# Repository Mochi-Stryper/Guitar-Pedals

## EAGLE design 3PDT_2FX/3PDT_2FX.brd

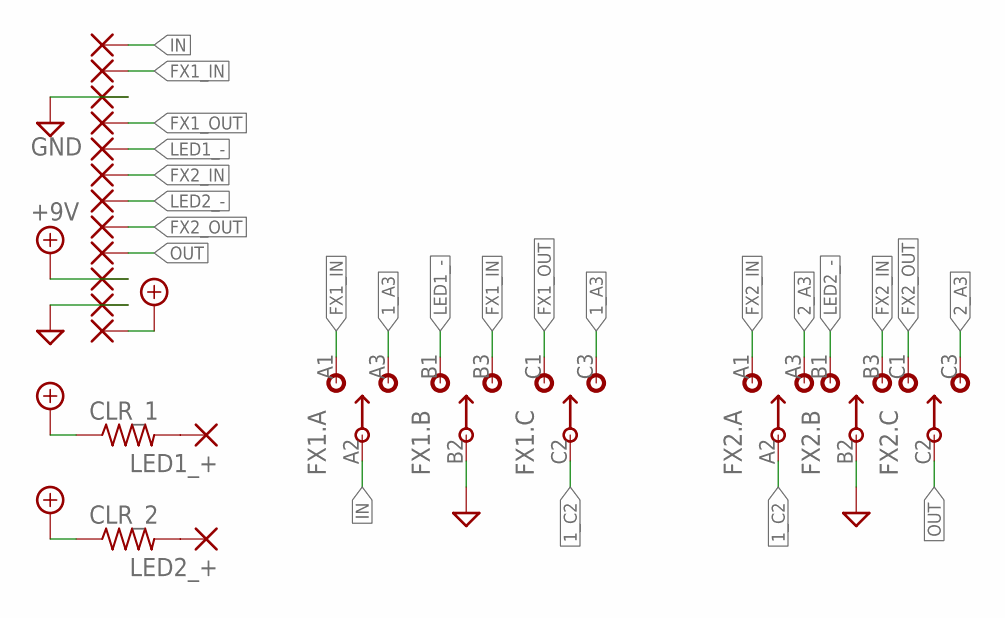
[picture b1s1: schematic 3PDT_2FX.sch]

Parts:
+9V, +9V1: 1,6/0,8
CLR_1, CLR_2: R-US_R0603; R0603
FX1, FX2: 3PDT.LUGS
FX1_IN, FX1_OUT, FX2_IN, FX2_OUT: 1,6/0,8
GND: 1,6/0,8
IN: 1,6/0,8
LED1_+, LED1_-, LED2_+, LED2_-: 1,6/0,8
OUT: 1,6/0,8
PAD3: 1,6/0,8

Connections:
1_A3: FX1.A3 (3), FX1.C3 (3)
1_C2: FX1.C2 (2), FX2.A2 (2)
2_A3: FX2.A3 (3), FX2.C3 (3)
+9V: +9V.1, +9V1.1, CLR_1.1, CLR_2.1
FX1_IN: FX1.A1 (1), FX1.B3 (3), FX1_IN.1
FX1_OUT: FX1.C1 (1), FX1_OUT.1
FX2_IN: FX2.A1 (1), FX2.B3 (3), FX2_IN.1
FX2_OUT: FX2.C1 (1), FX2_OUT.1
GND: FX1.B2 (2), FX2.B2 (2), GND.1, PAD3.1
IN: FX1.A2 (2), IN.1
LED1_-: FX1.B1 (1), LED1_-.1
LED2_-: FX2.B1 (1), LED2_-.1
unnamed: CLR_1.2, LED1_+.1
unnamed: CLR_2.2, LED2_+.1
OUT: FX2.C2 (2), OUT.1

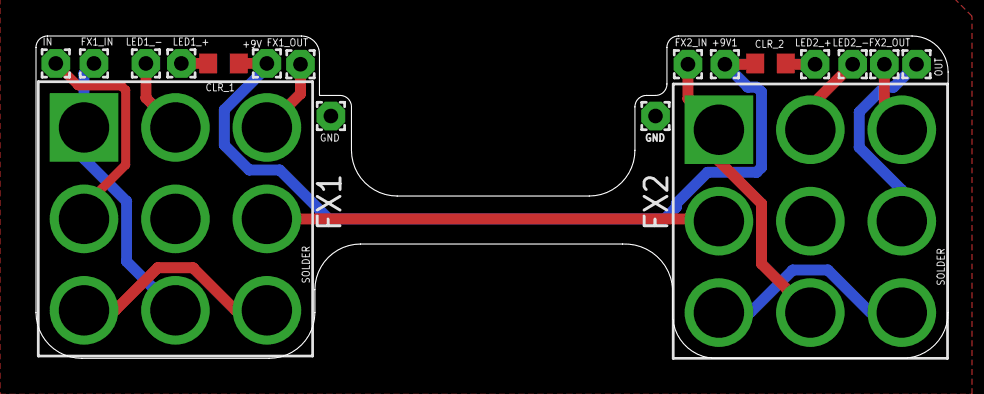
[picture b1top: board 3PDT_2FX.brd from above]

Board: 2 copper layers, 50.7 x 17.9 mm, 18 parts (0 on the bottom side), 15 nets.

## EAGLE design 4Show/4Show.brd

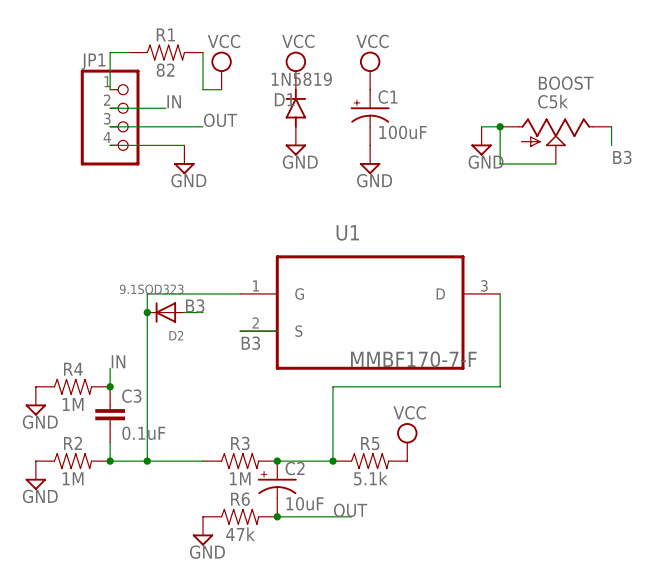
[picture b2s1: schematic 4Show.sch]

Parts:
BOOST: C5k; 9MM_SNAP-IN_POT
C1: 100uF; PAN_B_SMD+THRU
C2: 10uF; PAN_B_SMD+THRU
C3: 0.1uF; 0603
D1: 1N5819; SOD123
D2: 9.1SOD323; SOD-323F
JP1: PINHD-1X4; 1X04
R1: 82; 0603
R2, R3, R4: 1M; 0603
R5: 5.1k; 0603
R6: 47k; 0603
U1: MMBF170-7-F; SOT103P240X110-3N

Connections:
B3: BOOST.3 (E), D2.A, U1.2 (S)
GND: BOOST.1 (A), BOOST.2 (S), C1.-, C1.-- (-), D1.A, JP1.4, R2.1, R4.1, R6.1
IN: C3.1, JP1.2, R4.2
unnamed: JP1.1, R1.1
unnamed: C3.2, D2.C, R2.2, R3.1, U1.1 (G)
unnamed: C2.+, C2.++ (+), R3.2, R5.1, U1.3 (D)
OUT: C2.-, C2.-- (-), JP1.3, R6.2
VCC: C1.+, C1.++ (+), D1.C, R1.2, R5.2

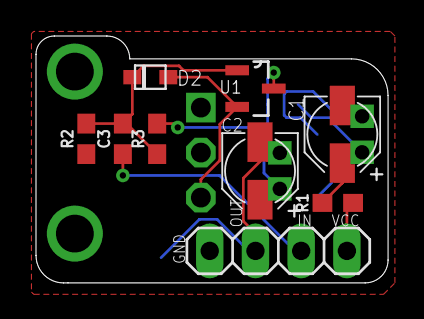
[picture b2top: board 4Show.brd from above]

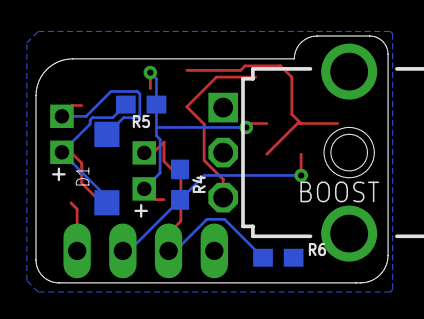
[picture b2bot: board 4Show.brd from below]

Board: 2 copper layers, 19.6 x 13.7 mm, 14 parts (5 on the bottom side), 8 nets.

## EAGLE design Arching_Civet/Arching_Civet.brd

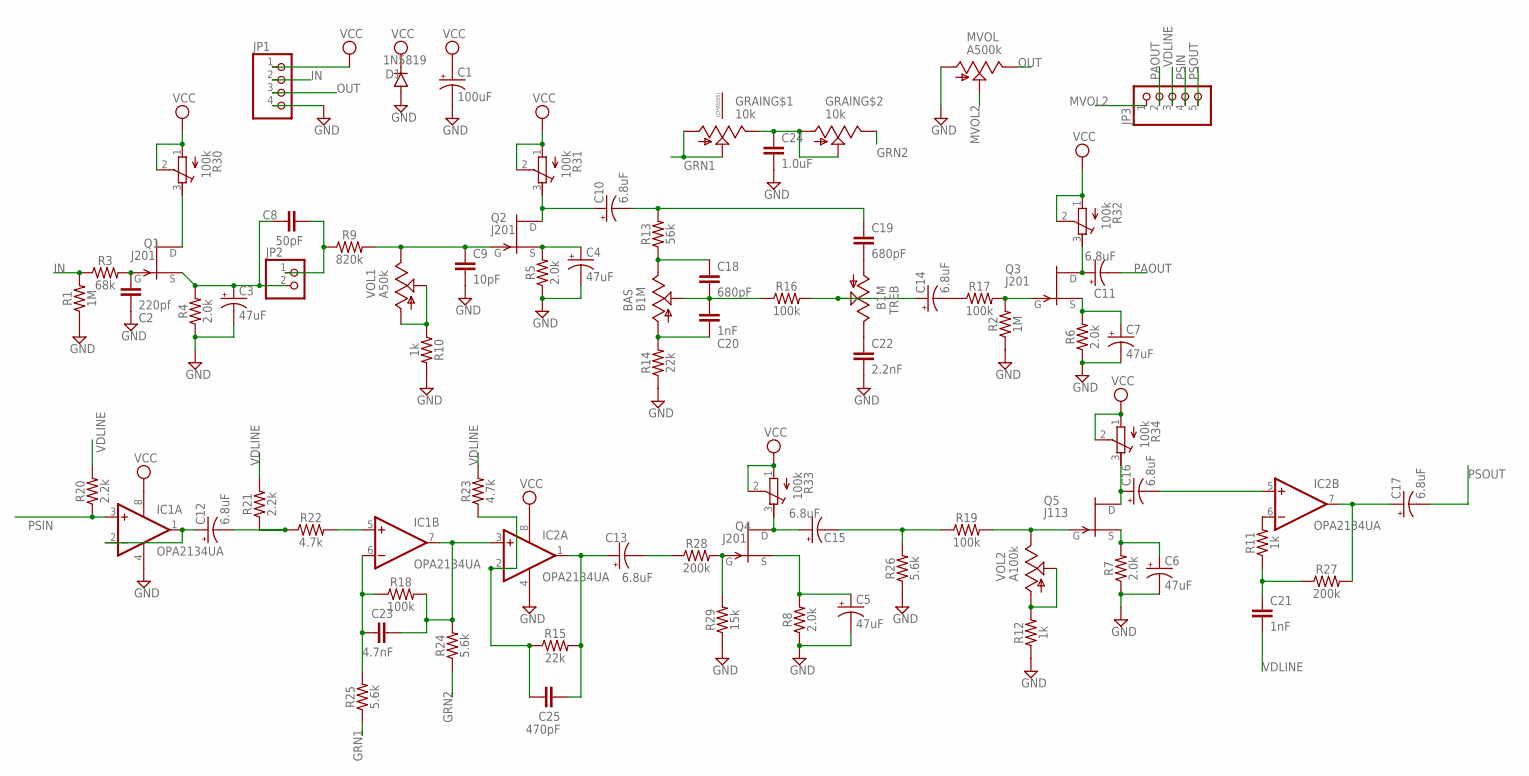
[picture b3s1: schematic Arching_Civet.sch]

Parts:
BAS: B1M; 9MM_SNAP-IN_POT
C1: 100uF; PAN_B_SMD+THRU
C2: 220pf; 0603
C3, C4, C5, C6, C7: 47uF; PAN_B_SMD+THRU
C8: 50pF; 0603
C9: 10pF; 0603
C10, C11, C12, C13, C14, C15, C16, C17: 6.8uF; PAN_B_SMD+THRU
C18, C19: 680pF; 0603
C20, C21: 1nF; 0603
C22: 2.2nF; 0603
C23: 4.7nF; 0603
C24: 1.0uF; 0603
C25: 470pF; 0603
D1: 1N5819; SOD123
GRAIN: 10k; DUAL_9MM_SNAP-IN_POT
IC1, IC2: OPA2134UA; SO08
JP1: PINHD-1X4; 1X04
JP2: PINHD-1X2; 1X02
JP3: PINHD-1X5; 1X05
MVOL: A500k; 9MM_SNAP-IN_POT
Q1, Q2, Q3, Q4: J201; SOT23
Q5: J113; SOT23
R1, R2: 1M; 0603
R3: 68k; 0603
R4, R5, R6, R7, R8: 2.0k; 0603
R9: 820k; 0603
R10, R11, R12: 1k; 0603
R13: 56k; 0603
R14, R15: 22k; 0603
R16, R17, R18, R19: 100k; 0603
R20, R21: 2.2k; 0603
R22, R23: 4.7k; 0603
R24, R25, R26: 5.6k; 0603
R27, R28: 200k; 0603
R29: 15k; 0603
R30, R31, R32, R33, R34: 100k; RTRIM3296W
TREB: B1M; 9MM_SNAP-IN_POT
VOL1: A50k; 9MM_SNAP-IN_POT
VOL2: A100k; 9MM_SNAP-IN_POT

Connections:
GND: C1.-, C1.-- (-), C2.2, C3.-, C3.-- (-), C4.-, C4.-- (-), C5.-, C5.-- (-), C6.-, C6.-- (-), C7.-, C7.-- (-), C9.2, C22.2, C24.2, D1.A, IC1.4 (V-), IC2.4 (V-), JP1.4, MVOL.1 (A), R1.1, R2.1, R4.1, R5.1, R6.1, R7.1, R8.1, R10.2, R12.1, R14.1, R26.1, R29.1
GRN1: GRAIN.1 (A), GRAIN.2 (S), R25.1
GRN2: GRAIN.3B (E), R24.1
IN: JP1.2, R1.2, R3.1
MVOL2: JP3.1, MVOL.2 (S)
unnamed: C2.1, Q1.3 (G), R3.2
unnamed: Q1.1 (D), R30.3 (E)
unnamed: C3.+, C3.++ (+), C8.1, JP2.2, Q1.2 (S), R4.2
unnamed: C8.2, JP2.1, R9.1
unnamed: R10.1, VOL1.1 (A), VOL1.2 (S)
unnamed: C9.1, Q2.3 (G), R9.2, VOL1.3 (E)
unnamed: C10.+, C10.++ (+), Q2.1 (D), R31.3 (E)
unnamed: C4.+, C4.++ (+), Q2.2 (S), R5.2
unnamed: C10.-, C10.-- (-), C19.1, R13.2
unnamed: BAS.3 (E), C18.1, R13.1
unnamed: BAS.1 (A), C20.2, R14.2
unnamed: BAS.2 (S), C18.2, C20.1, R16.1
unnamed: C22.1, TREB.3 (E)
unnamed: C19.2, TREB.1 (A)
unnamed: C14.+, C14.++ (+), R16.2, TREB.2 (S)
unnamed: C14.-, C14.-- (-), R17.1
unnamed: Q3.3 (G), R2.2, R17.2
unnamed: C7.+, C7.++ (+), Q3.2 (S), R6.2
unnamed: C11.+, C11.++ (+), Q3.1 (D), R32.3 (E)
unnamed: C12.+, C12.++ (+), IC1.1 (OUT), IC1.2 (-IN)
unnamed: C12.-, C12.-- (-), R21.1, R22.1
unnamed: IC1.5 (+IN), R22.2
unnamed: C23.1, IC1.6 (-IN), R18.1, R25.2
unnamed: C23.2, IC1.7 (OUT), IC2.3 (+IN), R18.2, R24.2
unnamed: C24.1, GRAIN.1B (A), GRAIN.2B (S), GRAIN.3 (E)
unnamed: C25.1, IC2.2 (-IN), R15.1, R23.1
unnamed: C13.+, C13.++ (+), C25.2, IC2.1 (OUT), R15.2
unnamed: C13.-, C13.-- (-), R28.1
unnamed: Q4.3 (G), R28.2, R29.2
unnamed: C5.+, C5.++ (+), Q4.2 (S), R8.2
unnamed: C15.+, C15.++ (+), Q4.1 (D), R33.3 (E)
unnamed: Q5.3 (G), R19.2, VOL2.3 (E)
unnamed: C15.-, C15.-- (-), R19.1, R26.2
unnamed: C6.+, C6.++ (+), Q5.2 (S), R7.2
unnamed: C16.-, C16.-- (-), IC2.5 (+IN)
unnamed: C16.+, C16.++ (+), Q5.1 (D), R34.3 (E)
unnamed: IC2.6 (-IN), R11.2
unnamed: C21.1, R11.1, R27.1
unnamed: C17.+, C17.++ (+), IC2.7 (OUT), R27.2
unnamed: R12.2, VOL2.1 (A), VOL2.2 (S)
OUT: JP1.3, MVOL.3 (E)
PAOUT: C11.-, C11.-- (-), JP3.2
PSIN: IC1.3 (+IN), JP3.4, R20.1
PSOUT: C17.-, C17.-- (-), JP3.5
VCC: C1.+, C1.++ (+), D1.C, IC1.8 (V+), IC2.8 (V+), JP1.1, R30.1 (A), R30.2 (S), R31.1 (A), R31.2 (S), R32.1 (A), R32.2 (S), R33.1 (A), R33.2 (S), R34.1 (A), R34.2 (S)
VDLINE: C21.2, JP3.3, R20.2, R21.2, R23.2

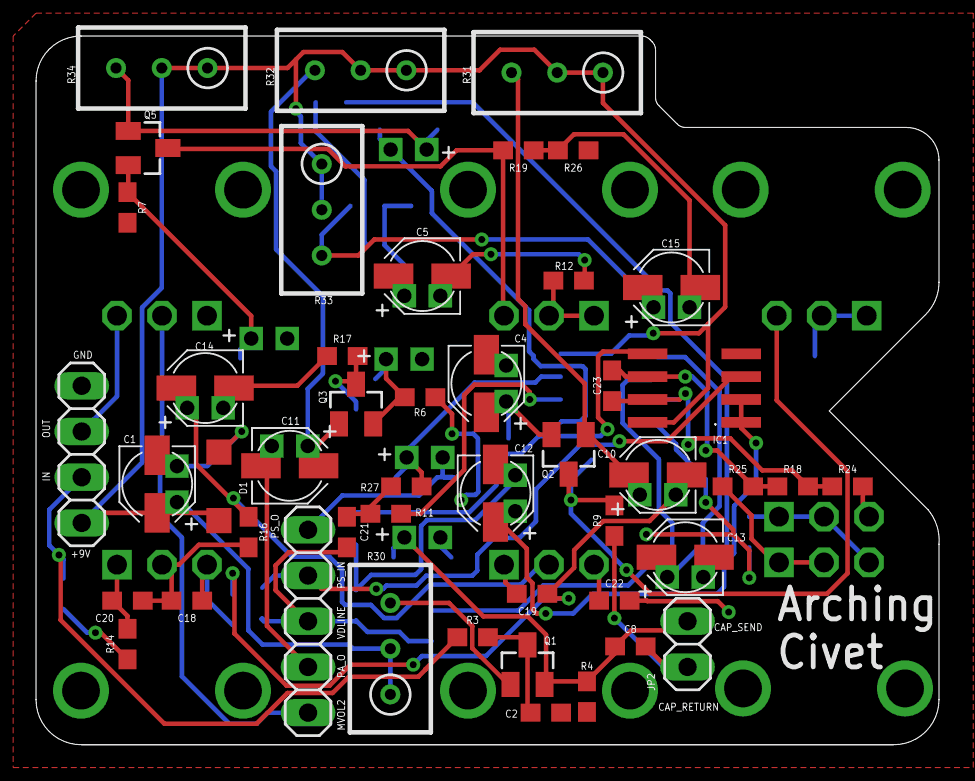
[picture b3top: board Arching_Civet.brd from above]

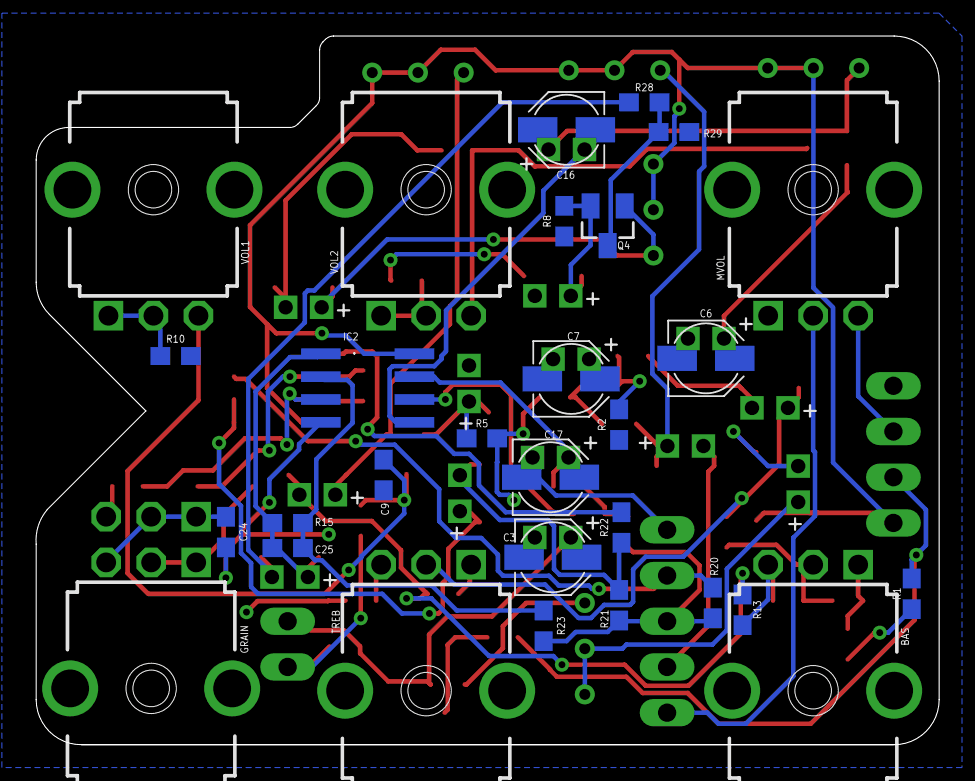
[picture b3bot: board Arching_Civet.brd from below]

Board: 2 copper layers, 50.2 x 39.4 mm, 76 parts (29 on the bottom side), 51 nets.

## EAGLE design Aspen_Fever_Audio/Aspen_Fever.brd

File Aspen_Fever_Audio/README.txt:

Aspen Fever
A stereo implementation of the FV-1 buffer used on the Madbean Pedals HeadTrip

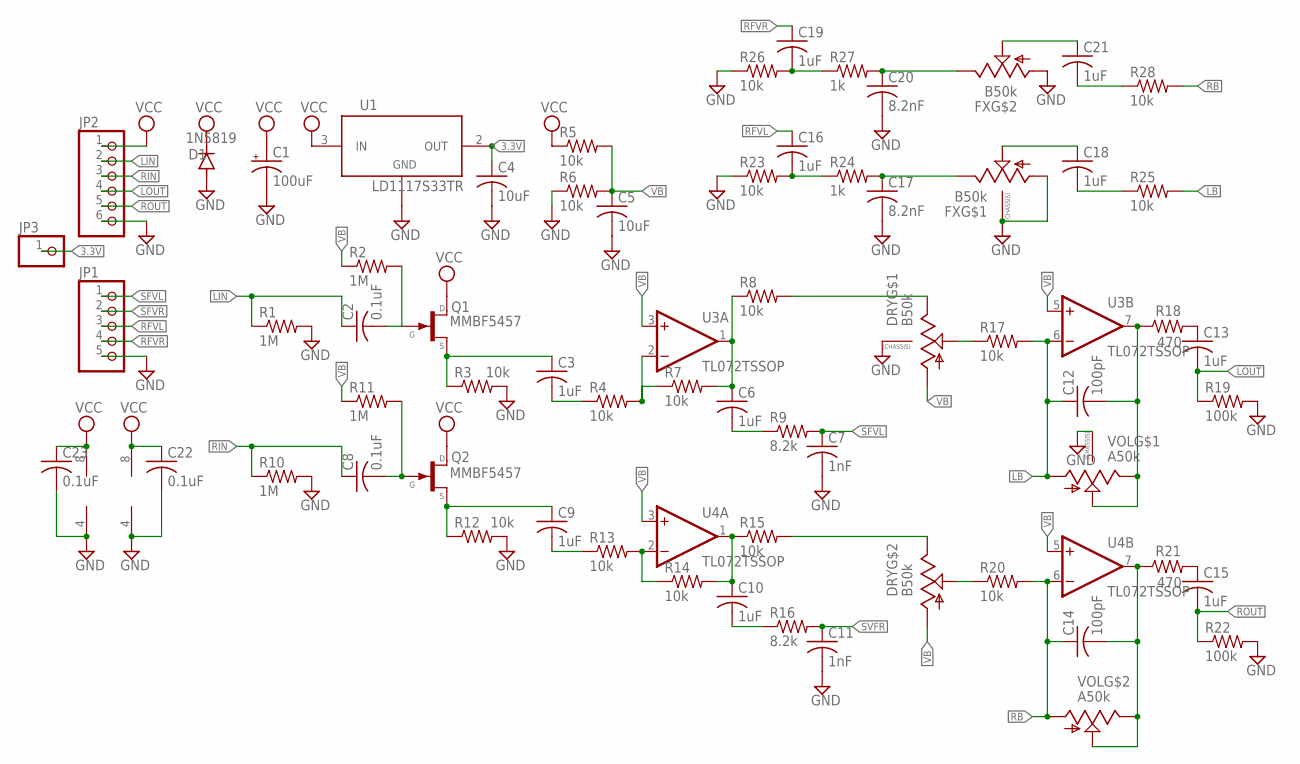
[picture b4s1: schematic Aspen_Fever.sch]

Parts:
C1: 100uF; PAN_B_SMD+THRU
C2, C8, C22, C23: 0.1uF; C0402
C3, C6, C9, C10, C13, C15, C16, C18, C19, C21: 1uF; C0603
C4, C5: 10uF; C0805
C7, C11: 1nF; C0402
C12, C14: 100pF; C0402
C17, C20: 8.2nF; C0402
D1: 1N5819; SOD123
DRY: B50k; DUAL_9MM_SNAP-IN_POT
FX: B50k; DUAL_9MM_SNAP-IN_POT
JP1: PINHD-1X5; 1X05
JP2: PINHD-1X6; 1X06
JP3: PINHD-1X1; 1X01
Q1, Q2: MMBF5457; SOT23
R1, R2, R10, R11: 1M; R0402
R3, R4, R5, R6, R7, R8, R12, R13, R14, R15, R17, R20, R23, R25, R26, R28: 10k; R0402
R9, R16: 8.2k; R0402
R18, R21: 470; R0402
R19, R22: 100k; R0402
R24, R27: 1k; R0402
U1: LD1117S33TR; SOT-223
U3, U4: TL072TSSOP; TSSOP-8
VOL: A50k; DUAL_9MM_SNAP-IN_POT

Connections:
3.3V: C4.1, JP3.1, U1.2 (OUT), U1.4
GND: C1.-, C1.-- (-), C4.2, C5.2, C7.2, C11.2, C17.2, C20.2, C22.2, C23.2, D1.A, DRY.CHASSIS1, DRY.CHASSIS2, FX.1 (A), FX.1B (A), FX.CHASSIS1, FX.CHASSIS2, JP1.5, JP2.6, R1.2, R3.2, R6.1, R10.2, R12.2, R19.2, R22.2, R23.1, R26.1, U1.1 (ADJ/GND), U3.4 (V-), U4.4 (V-), VOL.CHASSIS1, VOL.CHASSIS2
LB: C12.1, R17.2, R25.2, U3.6 (-IN), VOL.1 (A)
LIN: C2.1, JP2.2, R1.1
LOUT: C13.2, JP2.4, R19.1
unnamed: C6.2, R9.1
unnamed: C2.2, Q1.3 (G), R2.2
unnamed: C3.1, Q1.2 (S), R3.1
unnamed: C3.2, R4.1
unnamed: R4.2, R7.1, U3.2 (-IN)
unnamed: C6.1, R7.2, R8.1, U3.1 (OUT)
unnamed: DRY.3 (E), R8.2
unnamed: C8.2, Q2.3 (G), R11.2
unnamed: C9.1, Q2.2 (S), R12.1
unnamed: R13.2, R14.1, U4.2 (-IN)
unnamed: C9.2, R13.1
unnamed: C10.1, R14.2, R15.1, U4.1 (OUT)
unnamed: DRY.3B (E), R15.2
unnamed: C10.2, R16.1
unnamed: DRY.2 (S), R17.1
unnamed: C13.1, R18.2
unnamed: C19.2, R26.2, R27.1
unnamed: C12.2, R18.1, U3.7 (OUT), VOL.2 (S), VOL.3 (E)
unnamed: C16.2, R23.2, R24.1
unnamed: DRY.2B (S), R20.1
unnamed: C14.2, R21.1, U4.7 (OUT), VOL.2B (S), VOL.3B (E)
unnamed: C15.1, R21.2
unnamed: C17.1, FX.3 (E), R24.2
unnamed: C18.2, R25.1
unnamed: C18.1, FX.2 (S)
unnamed: C20.1, FX.3B (E), R27.2
unnamed: C21.1, FX.2B (S)
unnamed: C21.2, R28.1
RB: C14.1, R20.2, R28.2, U4.6 (-IN), VOL.1B (A)
RFVL: C16.1, JP1.3
RFVR: C19.1, JP1.4
RIN: C8.1, JP2.3, R10.1
ROUT: C15.2, JP2.5, R22.1
SFVL: C7.1, JP1.1, R9.2
SFVR: JP1.2
SVFR: C11.1, R16.2
VB: C5.1, DRY.1 (A), DRY.1B (A), R2.1, R5.2, R6.2, R11.1, U3.3 (+IN), U3.5 (+IN), U4.3 (+IN), U4.5 (+IN)
VCC: C1.+, C1.++ (+), C22.1, C23.1, D1.C, JP2.1, Q1.1 (D), Q2.1 (D), R5.1, U1.3 (IN), U3.8 (V+), U4.8 (V+)

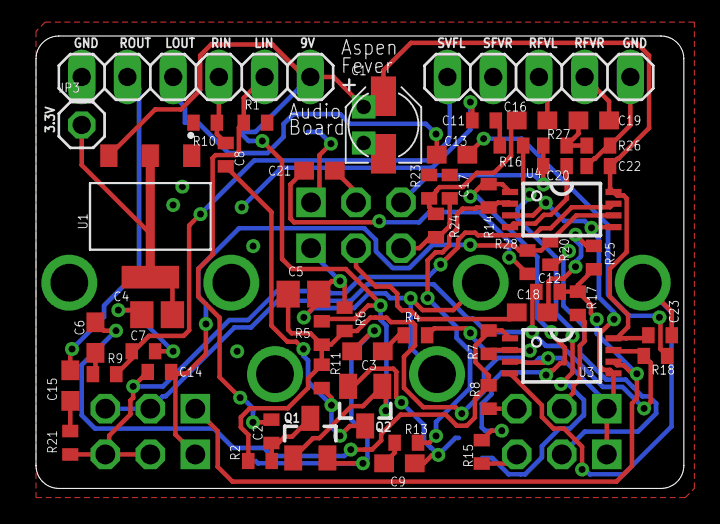
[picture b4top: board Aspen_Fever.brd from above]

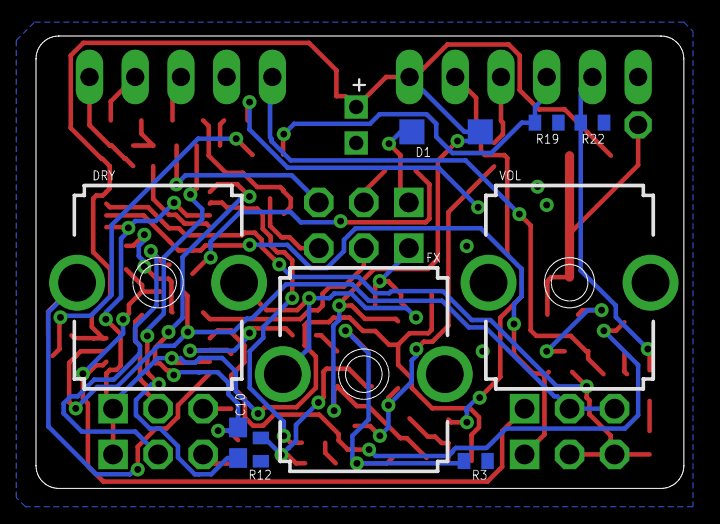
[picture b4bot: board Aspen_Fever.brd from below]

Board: 2 copper layers, 36.0 x 25.1 mm, 63 parts (9 on the bottom side), 42 nets.

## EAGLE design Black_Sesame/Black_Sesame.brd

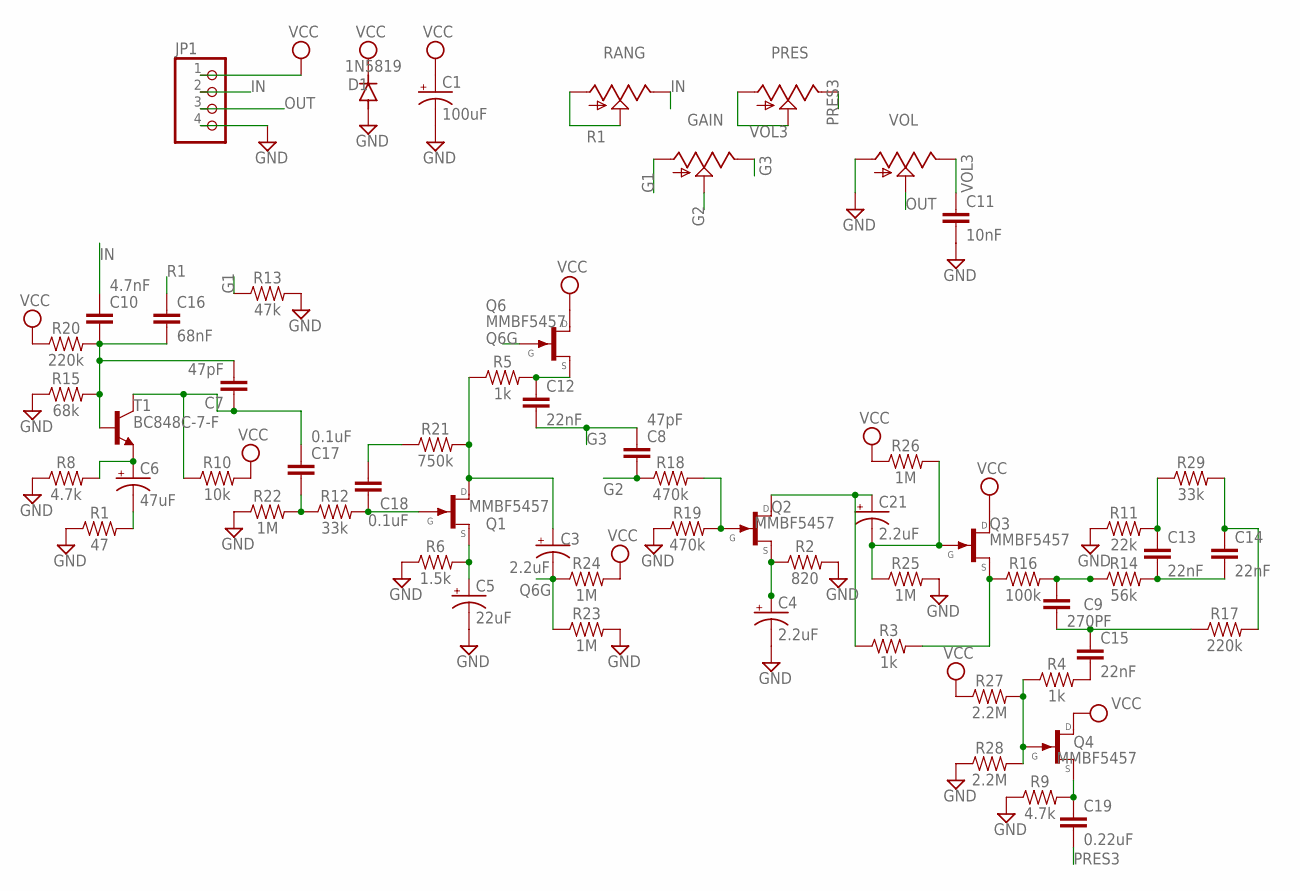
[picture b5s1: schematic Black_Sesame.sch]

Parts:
C1: 100uF; PAN_B_SMD+THRU
C3, C4, C21: 2.2uF; PAN_B_SMD+THRU
C5: 22uF; PAN_B_SMD+THRU
C6: 47uF; PAN_B_SMD+THRU
C7, C8: 47pF; 0603
C9: 270PF; 0603
C10: 4.7nF; 0603
C11: 10nF; 0603
C12, C13, C14, C15: 22nF; 0603
C16: 68nF; 0603
C17, C18: 0.1uF; 0603
C19: 0.22uF; 0603
D1: 1N5819; SOD123
GAIN: 9MM_SNAP-IN_POT_; 9MM_SNAP-IN_POT
JP1: PINHD-1X4; 1X04
PRES: 9MM_SNAP-IN_POT_; 9MM_SNAP-IN_POT
Q1, Q2, Q3, Q4, Q6: MMBF5457; SOT23
R1: 47; 0603
R2: 820; 0603
R3, R4, R5: 1k; 0603
R6: 1.5k; 0603
R8, R9: 4.7k; 0603
R10: 10k; 0603
R11: 22k; 0603
R12, R29: 33k; 0603
R13: 47k; 0603
R14: 56k; 0603
R15: 68k; 0603
R16: 100k; 0603
R17, R20: 220k; 0603
R18, R19: 470k; 0603
R21: 750k; 0603
R22, R23, R24, R25, R26: 1M; 0603
R27, R28: 2.2M; 0603
RANG: 9MM_SNAP-IN_POT_; 9MM_SNAP-IN_POT
T1: BC848C-7-F; SOT23-BEC
VOL: 9MM_SNAP-IN_POT_; 9MM_SNAP-IN_POT

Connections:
G1: GAIN.1 (A), R13.1
G2: C8.2, GAIN.2 (S), R18.1
G3: C8.1, C12.2, GAIN.3 (E)
GND: C1.-, C1.-- (-), C4.-, C4.-- (-), C5.-, C5.-- (-), C11.2, D1.A, JP1.4, R1.1, R2.2, R6.1, R8.1, R9.1, R11.1, R13.2, R15.1, R19.1, R22.1, R23.2, R25.2, R28.1, VOL.1 (A)
IN: C10.1, JP1.2, RANG.3 (E)
unnamed: C7.2, C10.2, C16.2, R15.2, R20.2, T1.B
unnamed: C7.1, C17.1, R10.1, T1.C
unnamed: C6.+, C6.++ (+), R8.2, T1.E
unnamed: C6.-, C6.-- (-), R1.2
unnamed: C17.2, R12.1, R22.2
unnamed: C18.1, Q1.3 (G), R12.2
unnamed: C3.+, C3.++ (+), Q1.1 (D), R5.1, R21.2
unnamed: C18.2, R21.1
unnamed: C5.+, C5.++ (+), Q1.2 (S), R6.2
unnamed: Q2.3 (G), R18.2, R19.2
unnamed: C12.1, Q6.2 (S), R5.2
unnamed: C4.+, C4.++ (+), Q2.2 (S), R2.1
unnamed: C21.-, C21.-- (-), Q3.3 (G), R25.1, R26.2
unnamed: C21.+, C21.++ (+), Q2.1 (D), R3.1
unnamed: Q3.2 (S), R3.2, R16.1
unnamed: C9.1, R14.1, R16.2
unnamed: C13.2, C14.2, R14.2
unnamed: C13.1, R11.2, R29.1
unnamed: C14.1, R17.2, R29.2
unnamed: C9.2, C15.1, R17.1
unnamed: C15.2, R4.2
unnamed: Q4.3 (G), R4.1, R27.2, R28.2
unnamed: C19.1, Q4.2 (S), R9.2
OUT: JP1.3, VOL.2 (S)
PRES3: C19.2, PRES.3 (E)
Q6G: C3.-, C3.-- (-), Q6.3 (G), R23.1, R24.1
R1: C16.1, RANG.1 (A), RANG.2 (S)
VCC: C1.+, C1.++ (+), D1.C, JP1.1, Q3.1 (D), Q4.1 (D), Q6.1 (D), R10.2, R20.1, R24.2, R26.1, R27.1
VOL3: C11.1, PRES.1 (A), PRES.2 (S), VOL.3 (E)

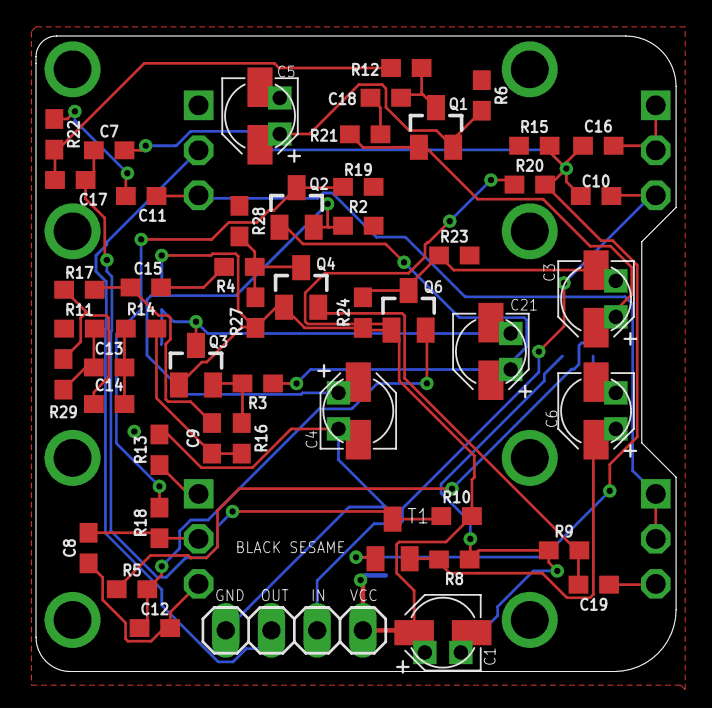
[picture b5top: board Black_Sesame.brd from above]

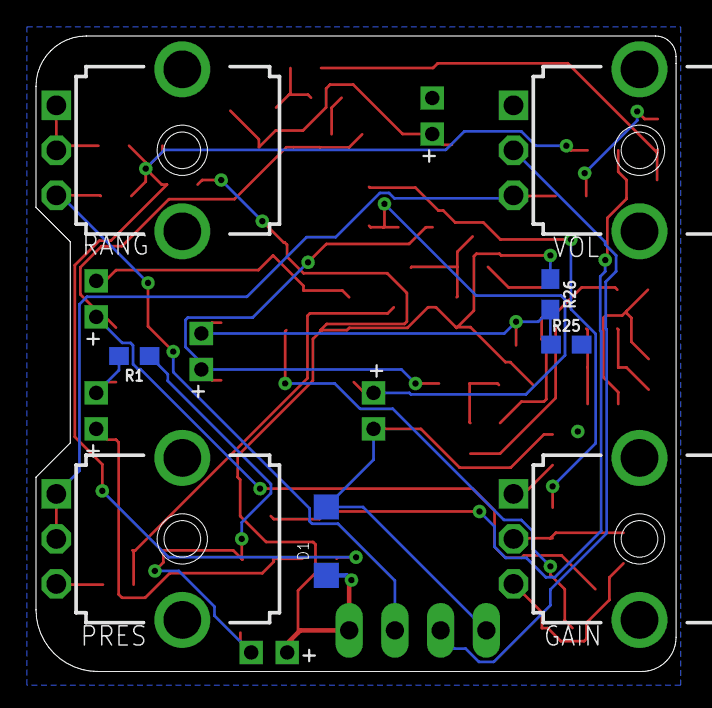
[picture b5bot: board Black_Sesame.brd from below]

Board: 2 copper layers, 35.6 x 35.3 mm, 59 parts (8 on the bottom side), 34 nets.

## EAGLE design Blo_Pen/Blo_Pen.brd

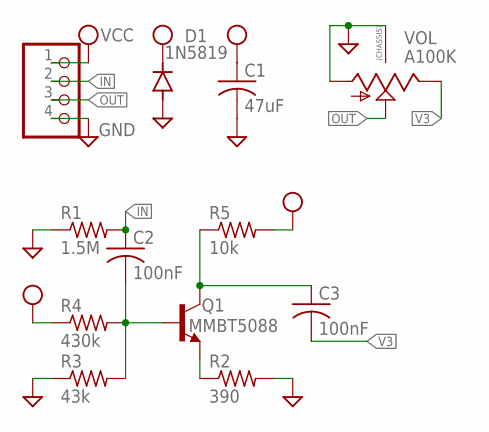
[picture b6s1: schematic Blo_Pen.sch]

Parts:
C1: 47uF; C1210
C2, C3: 100nF; C0603
D1: 1N5819; SOD123
JP1: PINHD-1X4; 1X04
Q1: MMBT5088; SOT23-BEC
R1: 1.5M; R0603
R2: 390; R0603
R3: 43k; R0603
R4: 430k; R0603
R5: 10k; R0603
VOL: A100K; 9MM_SNAP-IN_POT

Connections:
GND: C1.2, D1.A, JP1.4, R1.1, R2.2, R3.1, VOL.1 (A), VOL.CHASSIS1, VOL.CHASSIS2
IN: C2.1, JP1.2, R1.2
unnamed: C2.2, Q1.B, R3.2, R4.2
unnamed: Q1.E, R2.1
unnamed: C3.1, Q1.C, R5.1
OUT: JP1.3, VOL.2 (S)
V3: C3.2, VOL.3 (E)
VCC: C1.1, D1.C, JP1.1, R4.1, R5.2

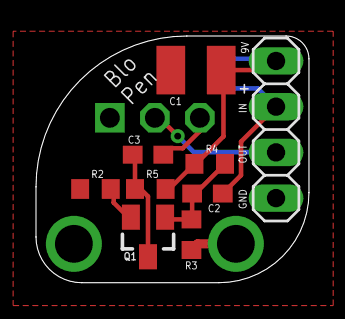
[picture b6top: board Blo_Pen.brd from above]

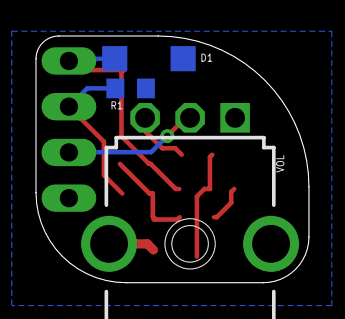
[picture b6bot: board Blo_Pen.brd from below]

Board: 2 copper layers, 15.2 x 13.7 mm, 12 parts (3 on the bottom side), 8 nets.

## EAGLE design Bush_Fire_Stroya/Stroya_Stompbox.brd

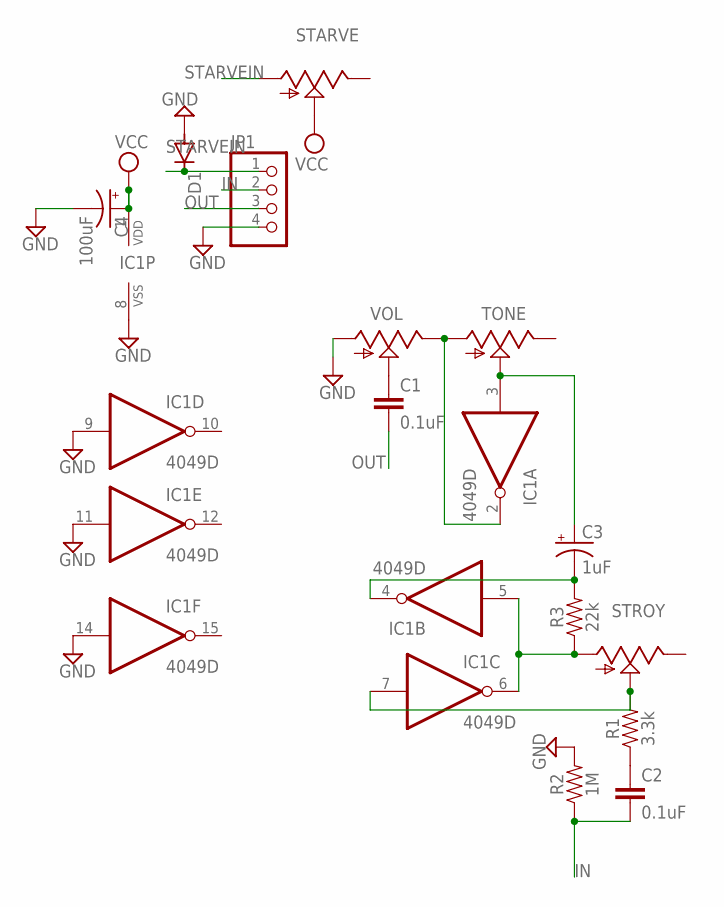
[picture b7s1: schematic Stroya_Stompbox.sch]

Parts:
C1, C2: 0.1uF; 0603
C3: 1uF; PAN_B_SMD+THRU
C4: 100uF; PAN_B_SMD+THRU
D1: DIODE-SOD123; SOD123
IC1: 4049D; SO16
JP1: PINHD-1X4; 1X04
R1: 3.3k; 0603
R2: 1M; 0603
R3: 22k; 0603
STARVE: 9MM_SNAP-IN_POT_; 9MM_SNAP-IN_POT
STROY: 9MM_SNAP-IN_POT_; 9MM_SNAP-IN_POT
TONE: 9MM_SNAP-IN_POT_; 9MM_SNAP-IN_POT
VOL: 9MM_SNAP-IN_POT_; 9MM_SNAP-IN_POT

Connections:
GND: C4.-, C4.-- (-), D1.A, IC1.8 (VSS), IC1.9 (I), IC1.11 (I), IC1.14 (I), JP1.4, R2.2, VOL.1 (A)
IN: C2.2, JP1.2, R2.1
unnamed: C2.1, R1.1
unnamed: IC1.7 (I), R1.2, STROY.2 (S)
unnamed: IC1.5 (I), IC1.6 (O), R3.1, STROY.1 (A)
unnamed: C3.+, C3.++ (+), IC1.3 (I), TONE.2 (S)
unnamed: IC1.2 (O), TONE.1 (A), VOL.3 (E)
unnamed: C1.1, VOL.2 (S)
unnamed: C3.-, C3.-- (-), IC1.4 (O), R3.2
OUT: C1.2, JP1.3
STARVEIN: D1.C, JP1.1, STARVE.1 (A)
VCC: C4.+, C4.++ (+), IC1.1 (VDD), STARVE.2 (S)

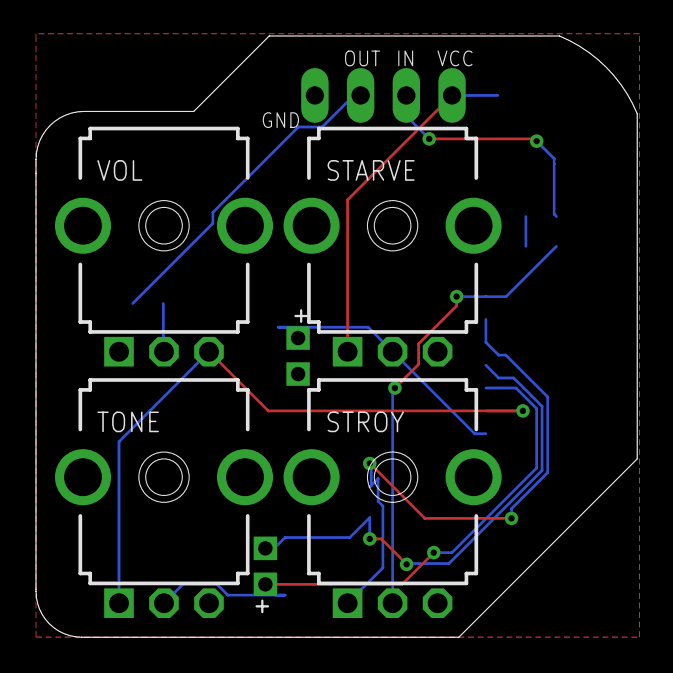
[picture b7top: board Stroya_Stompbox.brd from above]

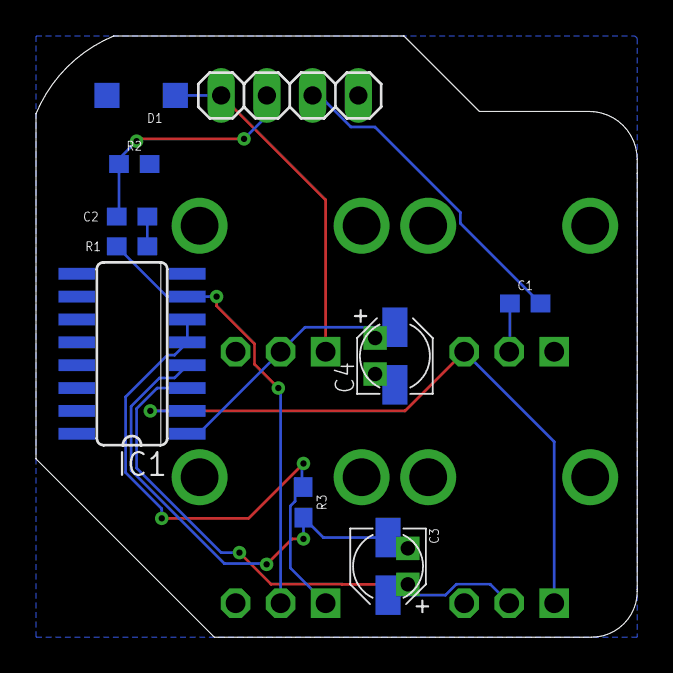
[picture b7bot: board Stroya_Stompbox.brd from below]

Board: 2 copper layers, 33.4 x 33.4 mm, 14 parts (10 on the bottom side), 12 nets.

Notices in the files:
parts and their libraries:
SparkFun-Capacitors: Licensing: Creative Commons ShareAlike 4.0 International - https://creativecommons.org/licenses/by-sa/4.0
